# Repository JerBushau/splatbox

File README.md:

# Splatbox Fightstick

A prototype for a split ergonomic fightstick inspired by [Flatbox](https://github.com/jfedor2/flatbox). Designed to provide a more ergonomic and comfortable DIY option for anyone that might be interested in such a thing. This project also serves as an opportunity for me to do some handwiring and learn Autodesk Fusion and KiCad.

## BOM

- PCB
- Waveshare rp2040 zero
- 13 x choc switches (pictured are [LowProKBs Twilight switches](https://lowprokb.ca/collections/switches/products/ambients-silent-choc-switches?variant=44873426436260))
- 2 x tact switches (Start and Select buttons)
- 8 x M3 6mm screws
- 8 x M3 heat-set inserts
- 28 awg ribbon cable (at least 7 pin)
- 3D printed case (minimal)
- 11 x Small 3D printed [button caps](https://github.com/jfedor2/flatbox/tree/master/3d-printed-buttoncaps)
- 2 x Big 3D printed [button caps](https://github.com/jfedor2/flatbox/tree/master/3d-printed-buttoncaps)
- Rubber feet

## Building

While still far from a finished product, the pcb certainly adds to the stability and reliability of the build. The tolerances for the case files are extremely tight, so you will likely need to scale it up some small fraction, I had to sand the pcb a bit to get a good fit.

- Set heat-set inserts in case
- Solder rp2040 zero
- Solder switches
- Solder ribbon cable to one side or the other
- Feed cable through the holes and solder the remaining side
- Screw the pcb to the case

## TODO:

- [x] PCB design: Create a custom PCB to improve durability and simplify the design
- [x] Case re-design to accommodate the PCB layout
  - [ ] More case options
- [ ] More modularity: Implement a way to extend or shorten the cable
- [ ] Wireless version (dongle approach): Explore a wireless setup using XIAO Seeeds

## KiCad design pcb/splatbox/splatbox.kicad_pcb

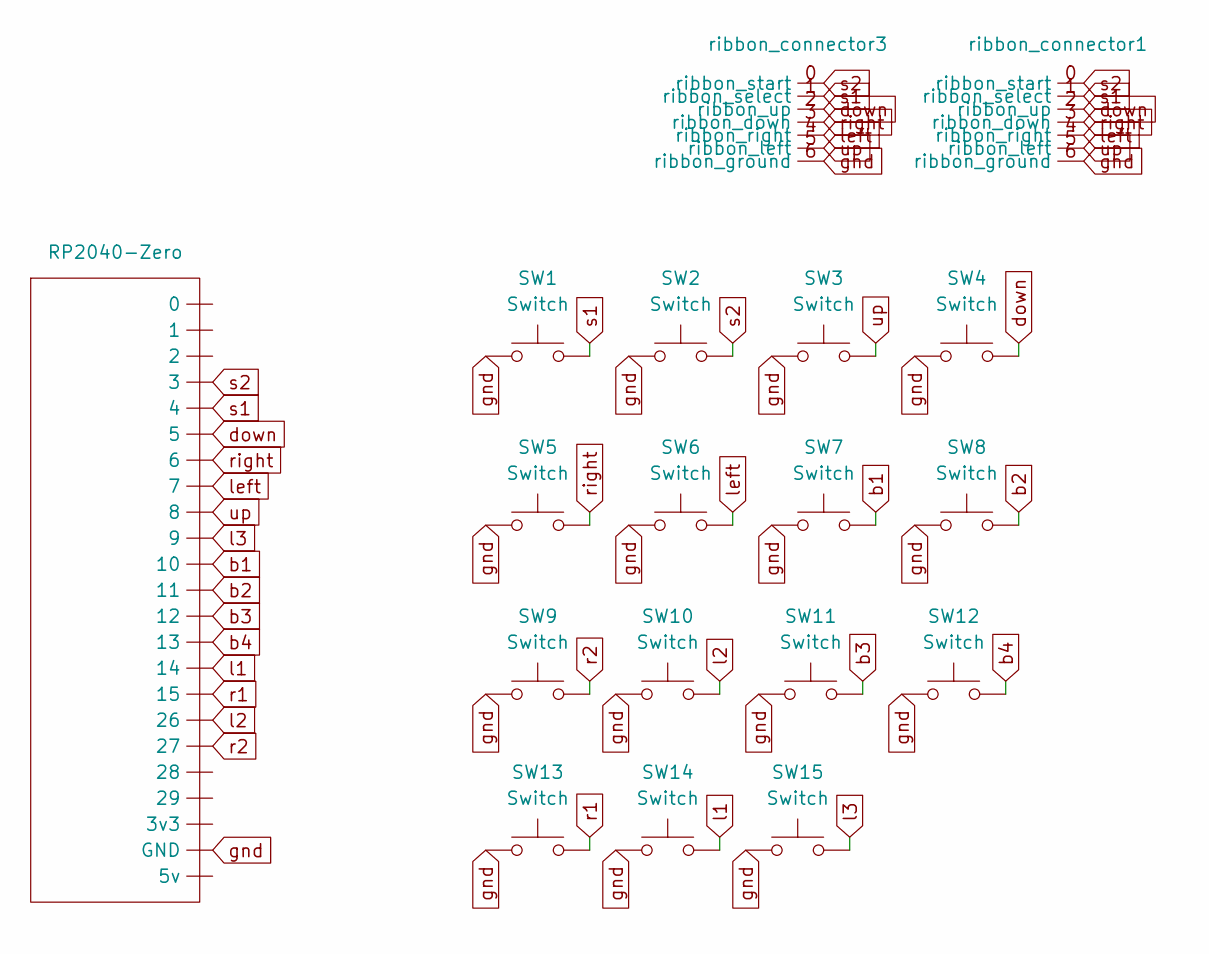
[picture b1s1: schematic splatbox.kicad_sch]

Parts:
SW1, SW2: Switch; SW_PUSH_6mm
SW3, SW4, SW5, SW6, SW7, SW8, SW9, SW10, SW11, SW12, SW13, SW14, SW15: Switch; Kailh_socket_PG1350_optional
U1: RP2040-Zero
ribbon_connector1, ribbon_connector3: ribbon connector

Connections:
b1: SW7.2, U1.10
b2: SW8.2, U1.11
b3: SW11.2, U1.12
b4: SW12.2, U1.13
down: SW4.2, U1.5, ribbon_connector1.2 (ribbon_up), ribbon_connector3.2 (ribbon_up)
gnd: SW1.1, SW2.1, SW3.1, SW4.1, SW5.1, SW6.1, SW7.1, SW8.1, SW9.1, SW10.1, SW11.1, SW12.1, SW13.1, SW14.1, SW15.1, U1.GND, ribbon_connector1.6 (ribbon_ground), ribbon_connector3.6 (ribbon_ground)
l1: SW14.2, U1.14
l2: SW10.2, U1.26
l3: SW15.2, U1.9
left: SW6.2, U1.7, ribbon_connector1.4 (ribbon_right), ribbon_connector3.4 (ribbon_right)
r1: SW13.2, U1.15
r2: SW9.2, U1.27
right: SW5.2, U1.6, ribbon_connector1.3 (ribbon_down), ribbon_connector3.3 (ribbon_down)
s1: SW1.2, U1.4, ribbon_connector1.1 (ribbon_select), ribbon_connector3.1 (ribbon_select)
s2: SW2.2, U1.3, ribbon_connector1.0 (ribbon_start), ribbon_connector3.0 (ribbon_start)
up: SW3.2, U1.8, ribbon_connector1.5 (ribbon_left), ribbon_connector3.5 (ribbon_left)

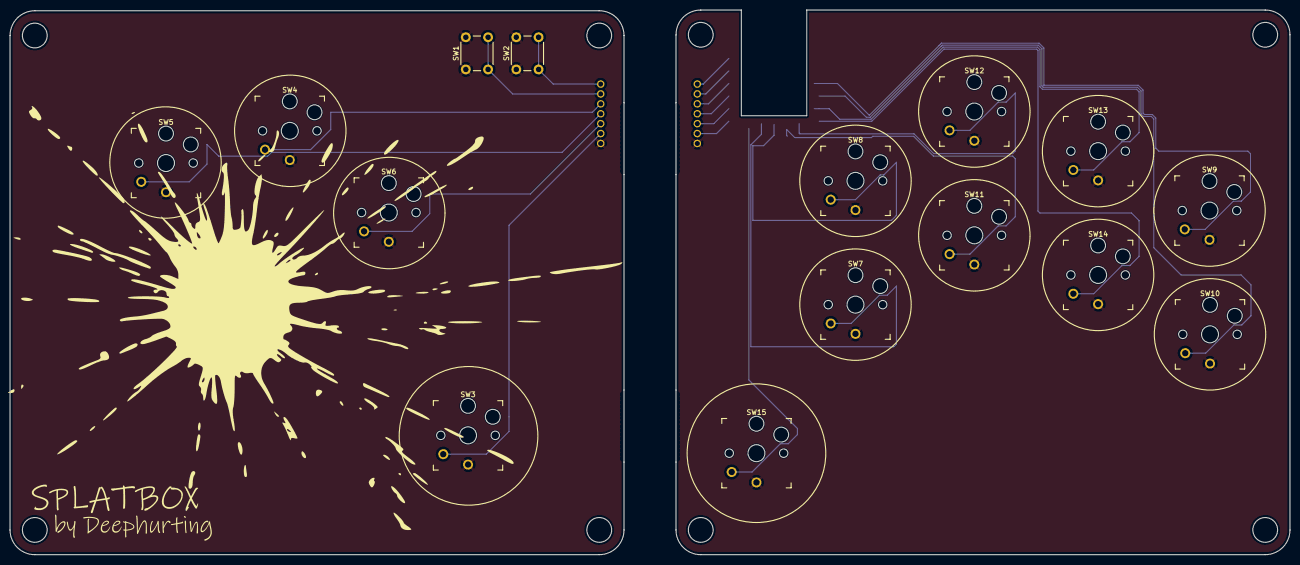
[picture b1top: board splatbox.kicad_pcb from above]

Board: 2 copper layers, 258.5 x 110.0 mm, 18 parts (0 on the bottom side), 16 nets.

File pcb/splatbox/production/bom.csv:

Designator,Footprint,Quantity,Value,LCSC Part #
"RIBBON_CONNECTOR1, RIBBON_CONNECTOR3",ribbon connector,2,~,
"SW1, SW2",SW_PUSH_6mm,2,Switch,
"SW10, SW11, SW12, SW13, SW14, SW15, SW3, SW4, SW5, SW6, SW7, SW8, SW9",Kailh_socket_PG1350_optional,13,Switch,
U1,RP2040-Zero,1,RP2040-Zero,

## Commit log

2024-12-08 Init
2024-12-08 Add README and photos
2024-12-08 Filename typo; Update README
2024-12-08 Update bom to include printing button caps
2024-12-14 First pass pcb - not working with JLC
2024-12-15 Add mousebites to connect panels; Add silk screen
2024-12-15 Remove todo
2024-12-15 Remove all except gerber
2024-12-22 Add pcb files; Add minimal case design; Add photos; Update readme
2024-12-22 Add step file for minimal case
2024-12-22 Reorganize folders a bit
2024-12-22 Add ugly case right side
2024-12-22 Add note about tolerance to readme
